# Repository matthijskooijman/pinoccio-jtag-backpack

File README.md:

Pinoccio JTAG backpack
----------------------
This repository contains the schematic and board files for a "JTAG / ICSP
backpack" for the [Pinoccio](http://pinocc.io) board. It allows easy access to
the pins used for in-circuit programming and JTAG programming and debugging
through standard 6 and 10-pin headers.

This project is created using Kicad. The board design was intended as a
single-layer design, with the back layer emulated using wire bridges (so
the vias have a big drill size - be sure to double-check that if you
produce this as a proper double-layer design).

For more background, see [this blogpost](http://www.stderr.nl/Blog/Hardware/Electronics/Pinoccio/JTAG.html).

License
-------
All content in this repository is licensed under the ["Beluki"
license][1]:

Permission is hereby granted, free of charge, to anyone obtaining a copy
of this document and accompanying files, to do whatever they want with
them without any restriction, including, but not limited to, copying,
modification and redistribution.

NO WARRANTY OF ANY KIND IS PROVIDED.

[1]: https://github.com/Beluki/License/blob/master/Documentation/License

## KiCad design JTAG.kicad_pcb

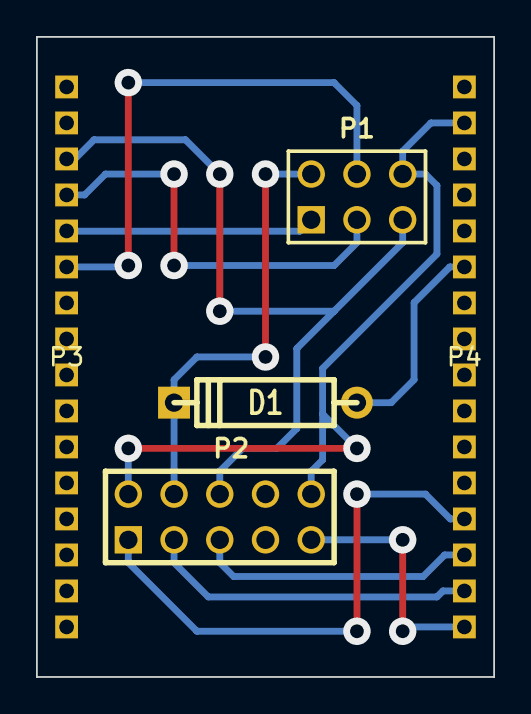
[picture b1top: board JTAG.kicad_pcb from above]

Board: 2 copper layers, 25.4 x 35.6 mm, 5 parts (0 on the bottom side), 11 nets.

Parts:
D1: DIODE; D4
P1: ICSP; pin_array_3x2
P2: AVR-JTAG; PIN_ARRAY_5x2
P3: PINOCCIO_HEADER_1; SIL-2.0mm-16
P4: PINOCCIO_HEADER_2; SIL-2.0mm-16

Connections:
unnamed: P2.1, P4.13
unnamed: P2.3, P4.15
unnamed: P2.5, P4.14
unnamed: P2.9, P4.16
unnamed: P1.1, P3.5
unnamed: P1.4, P3.6
unnamed: D1.2, P1.2, P2.4
unnamed: D1.1, P4.6
unnamed: P1.3, P3.4
unnamed: P1.5, P2.6, P3.3
unnamed: P1.6, P2.2, P2.10, P4.2

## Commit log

2014-09-16 Add README
2014-09-16 Add initial version of the design
    This project is created using Kicad. The board design was intended as a
    single-layer design, with the back layer emulated using wire bridges (so
    the vias have a big drill size - be sure to double-check that if you
    produce this as a proper double-layer design).
